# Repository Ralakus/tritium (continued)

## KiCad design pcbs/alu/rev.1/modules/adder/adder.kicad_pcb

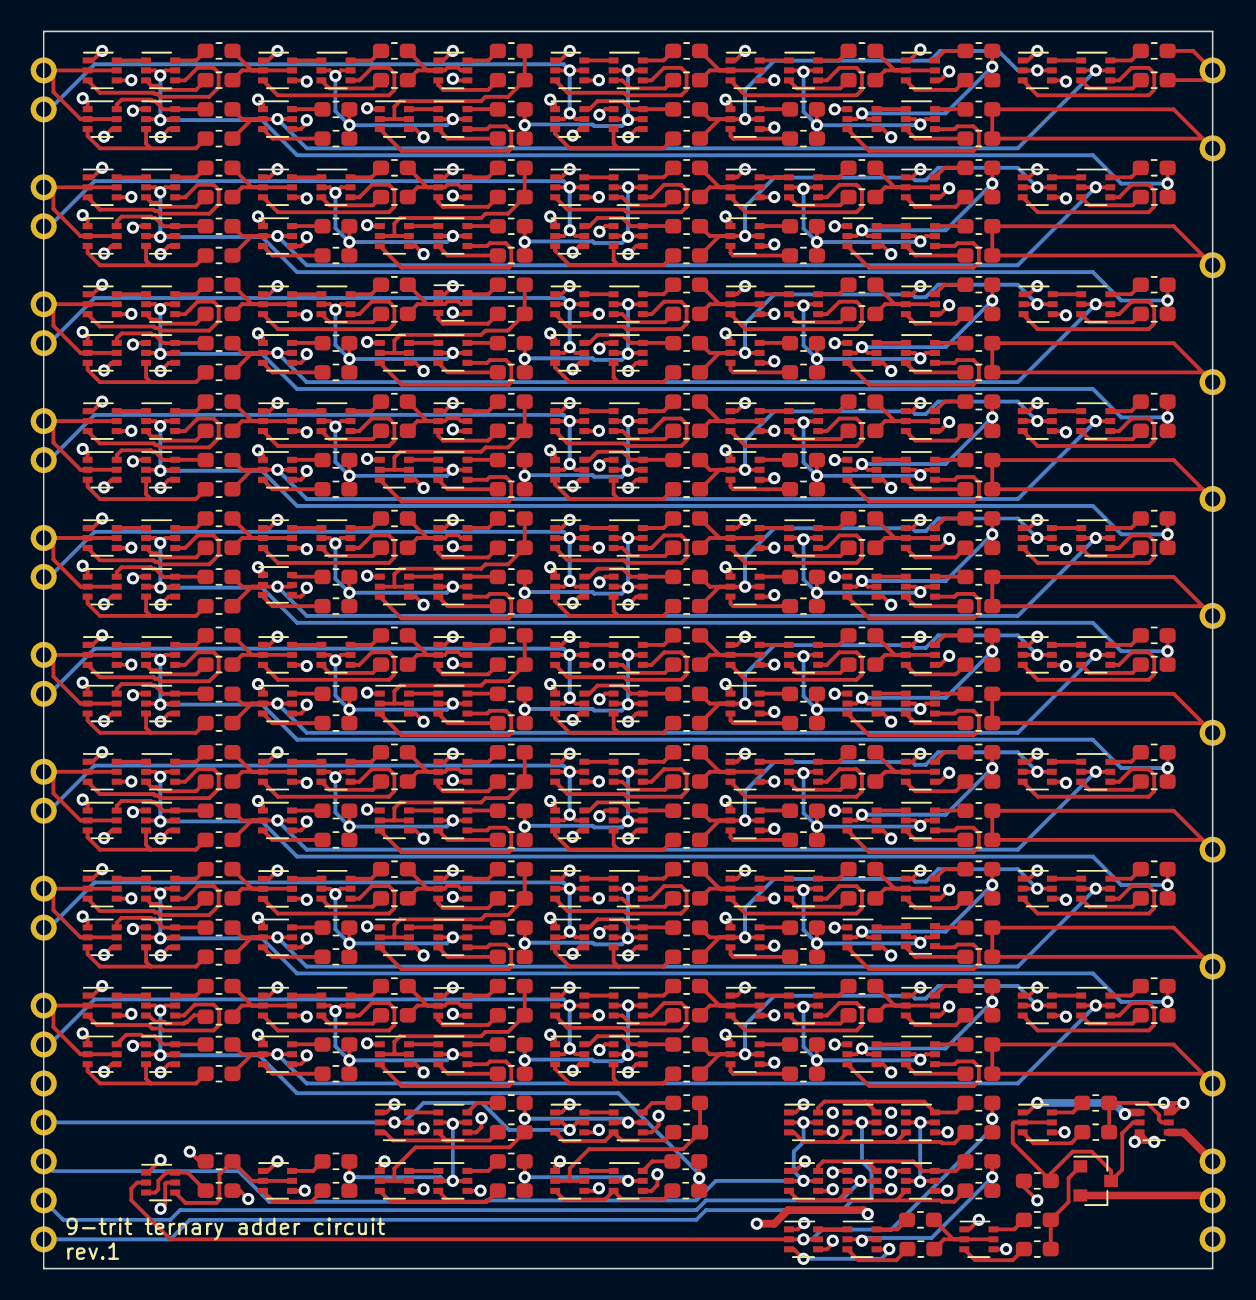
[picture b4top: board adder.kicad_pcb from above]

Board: 4 copper layers, 76.2 x 80.6 mm, 513 parts (0 on the bottom side), 544 nets.

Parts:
J1, J2, J3, J4, J5, J6, J7, J8, J9, J10, J11, J12, J13, J14, J15, J16, J17, J18, J19, J20, J21, J22, J23, J24, J25, J26, J27, J28, J29, J30, J31, J32, J33, J34, J35, J36: Conn_01x01; Edge_Castellation_1x01_P2.54
Q1, Q2, Q3, Q4, Q5, Q6, Q7, Q8, Q9, Q10, Q11, Q12, Q13, Q14, Q15, Q16, Q17, Q19, Q20, Q21, Q22, Q23, Q24, Q25, Q26, Q27, Q28, Q29, Q30, Q31, Q32, Q33, Q34, Q35, Q36, Q37, Q38, Q39, Q40, Q41, Q42, Q43, Q44, Q45, Q46, Q47, Q48, Q49, Q50, Q51, Q52, Q53, Q54, Q55, Q56, Q57, Q58, Q59, Q60, Q61, Q62, Q63, Q64, Q65, Q66, Q67, Q68, Q69, Q70, Q71, Q72, Q73, Q74, Q75, Q76, Q77, Q78, Q79, Q80, Q81, Q82, Q83, Q84, Q85, Q86, Q87, Q88, Q89, Q90, Q91, Q92, Q93, Q94, Q95, Q96, Q97, Q98, Q99, Q100, Q101, Q102, Q103, Q104, Q105, Q106, Q107, Q108, Q109, Q110, Q111, Q112, Q113, Q114, Q115, Q116, Q117, Q118, Q119, Q120, Q121, Q122, Q123, Q124, Q125, Q126, Q127, Q128, Q129, Q130, Q131, Q132, Q133, Q134, Q135, Q136, Q137, Q138, Q139, Q140, Q141, Q142, Q143, Q144, Q145, Q146, Q147, Q148, Q149, Q150, Q151, Q152, Q153, Q154, Q155, Q156, Q157, Q158, Q159, Q160, Q161, Q162, Q163, Q164, Q165, Q166, Q167, Q168, Q169, Q170, Q171, Q172, Q173, Q174, Q175, Q176, Q177, Q178, Q179, Q180, Q181, Q182, Q183, Q184, Q185, Q186, Q187, Q188, Q189, Q190, Q191, Q192, Q193, Q194, Q195, Q196, Q197, Q198, Q199, Q200, Q201, Q202, Q203, Q204, Q205, Q206, Q207, Q208, Q209, Q210, Q211, Q212, Q213, Q214, Q215, Q216, Q217, Q218, Q219, Q220: BSS8402DW; SOT-363_SC-70-6
Q18: 2N7002; SOT-23
R1, R3, R4, R5, R6, R7, R8, R9, R10, R11, R12, R13, R14, R15, R16, R17, R18, R19, R20, R21, R22, R23, R24, R25, R26, R27, R28, R29, R30, R31, R32, R33, R34, R35, R36, R37, R38, R39, R40, R41, R42, R43, R44, R45, R46, R47, R48, R49, R50, R51, R52, R53, R54, R55, R56, R57, R58, R59, R60, R61, R62, R63, R64, R65, R66, R67, R68, R69, R70, R71, R72, R73, R74, R75, R76, R77, R78, R79, R80, R81, R82, R83, R84, R85, R86, R87, R88, R89, R90, R91, R92, R93, R94, R95, R96, R97, R98, R99, R100, R101, R102, R103, R104, R105, R106, R107, R108, R109, R110, R111, R112, R113, R114, R115, R116, R117, R118, R119, R120, R121, R122, R123, R124, R125, R126, R127, R128, R129, R130, R131, R132, R133, R134, R135, R136, R137, R138, R139, R140, R141, R142, R143, R144, R145, R146, R147, R148, R149, R150, R151, R152, R153, R154, R155, R156, R157, R158, R159, R160, R161, R162, R163, R164, R165, R166, R167, R168, R169, R170, R171, R172, R173, R174, R175, R176, R177, R178, R179, R180, R181, R182, R183, R184, R185, R186, R187, R188, R189, R190, R191, R192, R193, R194, R195, R196, R197, R198, R199, R200, R201, R202, R203, R204, R205, R206, R207, R208, R209, R210, R211, R212, R213, R214, R215, R216, R217, R218, R219, R220, R221, R222, R223, R224, R225, R226, R227, R228, R229, R230, R231, R232, R233, R234, R235, R236, R237, R238, R239, R240, R241, R242, R243, R244, R245, R246, R247, R248, R249, R250, R251, R252, R253, R254, R255, R256, R257: 12k; R_0603_1608Metric_Pad1.05x0.95mm_HandSolder
R2: 470k; R_0603_1608Metric_Pad1.05x0.95mm_HandSolder

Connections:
/adder/CarryIn: Q29.2, Q29.5, Q32.2, Q32.5, R20.1, R21.2
/adder/Vdd: Q22.3, Q23.4, Q24.4, Q25.4, Q26.4, Q27.4, Q28.4, Q29.4, Q30.4, Q31.4, Q35.4, Q36.4, Q37.4, Q38.4, Q39.4, Q40.4, Q44.4, Q45.4, Q46.4, Q47.4, Q48.4, Q49.4, Q53.4, Q54.4, Q55.4, Q56.4, Q57.4, Q58.4, Q59.4, Q60.4, Q61.4, Q65.4, Q66.4, Q67.4, Q68.4, Q69.4, Q70.4, Q74.4, Q75.4, Q76.4, Q77.4, Q78.4, Q79.4, Q83.4, Q84.4, Q85.4, Q89.4, Q90.4, Q91.4, Q92.4, Q93.4, Q94.4, Q95.4, Q96.4, Q97.4, Q101.4, Q102.4, Q103.4, Q104.4, Q105.4, Q106.4, Q110.4, Q111.4, Q112.4, Q113.4, Q114.4, Q115.4, Q119.4, Q120.4, Q121.4, Q122.4, Q123.4, Q124.4, Q125.4, Q126.4, Q127.4, Q131.4, Q132.4, Q133.4, Q134.4, Q135.4, Q136.4, Q140.4, Q141.4, Q142.4, Q143.4, Q144.4, Q145.4, Q149.4, Q150.4, Q151.4, Q155.4, Q156.4, Q157.4, Q158.4, Q159.4, Q160.4, Q161.4, Q162.4, Q163.4, Q167.4, Q168.4, Q169.4, Q170.4, Q171.4, Q172.4, Q176.4, Q177.4, Q178.4, Q179.4, Q180.4, Q181.4, Q185.4, Q186.4, Q187.4, Q188.4, Q189.4, Q190.4, Q191.4, Q192.4, Q193.4, Q197.4, Q198.4, Q199.4, Q200.4, Q201.4, Q202.4, Q206.4, Q207.4, Q208.4, Q209.4, Q210.4, Q211.4, Q215.4, Q216.4, Q217.4
/adder/Vss: Q22.6, Q23.1, Q24.1, Q25.1, Q26.1, Q27.1, Q28.1, Q29.1, Q30.1, Q31.1, Q35.1, Q36.1, Q37.1, Q38.1, Q39.1, Q40.1, Q44.1, Q45.1, Q46.1, Q47.1, Q48.1, Q49.1, Q53.1, Q54.1, Q55.1, Q56.1, Q57.1, Q58.1, Q59.1, Q60.1, Q61.1, Q65.1, Q66.1, Q67.1, Q68.1, Q69.1, Q70.1, Q74.1, Q75.1, Q76.1, Q77.1, Q78.1, Q79.1, Q83.1, Q84.1, Q85.1, Q89.1, Q90.1, Q91.1, Q92.1, Q93.1, Q94.1, Q95.1, Q96.1, Q97.1, Q101.1, Q102.1, Q103.1, Q104.1, Q105.1, Q106.1, Q110.1, Q111.1, Q112.1, Q113.1, Q114.1, Q115.1, Q119.1, Q120.1, Q121.1, Q122.1, Q123.1, Q124.1, Q125.1, Q126.1, Q127.1, Q131.1, Q132.1, Q133.1, Q134.1, Q135.1, Q136.1, Q140.1, Q141.1, Q142.1, Q143.1, Q144.1, Q145.1, Q149.1, Q150.1, Q151.1, Q155.1, Q156.1, Q157.1, Q158.1, Q159.1, Q160.1, Q161.1, Q162.1, Q163.1, Q167.1, Q168.1, Q169.1, Q170.1, Q171.1, Q172.1, Q176.1, Q177.1, Q178.1, Q179.1, Q180.1, Q181.1, Q185.1, Q186.1, Q187.1, Q188.1, Q189.1, Q190.1, Q191.1, Q192.1, Q193.1, Q197.1, Q198.1, Q199.1, Q200.1, Q201.1, Q202.1, Q206.1, Q207.1, Q208.1, Q209.1, Q210.1, Q211.1, Q215.1, Q216.1, Q217.1
A0: J1.1, Q23.2, Q23.5, Q24.2, Q24.5
A1: J2.1, Q89.2, Q89.5, Q90.2, Q90.5
A2: J3.1, Q155.2, Q155.5, Q156.2, Q156.5
A3: J4.1, Q25.2, Q25.5, Q26.2, Q26.5
A4: J5.1, Q91.2, Q91.5, Q92.2, Q92.5
A5: J6.1, Q157.2, Q157.5, Q158.2, Q158.5
A6: J7.1, Q27.2, Q27.5, Q28.2, Q28.5
A7: J8.1, Q93.2, Q93.5, Q94.2, Q94.5
A8: J9.1, Q159.2, Q159.5, Q160.2, Q160.5
B0: J10.1, Q53.2, Q53.5, Q54.2, Q54.5
B1: J11.1, Q119.2, Q119.5, Q120.2, Q120.5
B2: J12.1, Q185.2, Q185.5, Q186.2, Q186.5
B3: J13.1, Q55.2, Q55.5, Q56.2, Q56.5
B4: J14.1, Q121.2, Q121.5, Q122.2, Q122.5
B5: J15.1, Q187.2, Q187.5, Q188.2, Q188.5
B6: J16.1, Q57.2, Q57.5, Q58.2, Q58.5
B7: J17.1, Q123.2, Q123.5, Q124.2, Q124.5
B8: J18.1, Q189.2, Q189.5, Q190.2, Q190.5
CarryIn: J20.1, Q9.2, Q9.5, Q13.2, Q13.5
CarryOut: J19.1, R256.1, R257.2
FnA0: J21.1, Q2.2, Q2.5, Q3.2, Q3.5
FnB0: J22.1, Q6.2, Q6.5
FnB1: J23.1, Q5.2, Q5.5
GND: J35.1, Q1.5, Q18.2, R2.1
unnamed: Q1.2, Q11.2, Q11.5, R5.1, R6.2
unnamed: Q1.3, Q1.6, R1.1
unnamed: Q1.4, Q4.2, Q4.5, R2.2
unnamed: Q2.3, Q5.3, Q7.3, R5.2
unnamed: Q2.6, Q5.6, Q7.6, R6.1
unnamed: Q3.3, Q6.3, Q8.3, R7.2
unnamed: Q3.6, Q6.6, Q8.6, R8.1
unnamed: Q4.3, R3.2
unnamed: Q4.6, R4.1
unnamed: Q9.6, Q10.1
unnamed: Q10.2, Q10.5, Q17.2, Q17.5, R3.1, R4.2
unnamed: Q9.3, Q10.3, R9.2
unnamed: Q10.6, R10.1
unnamed: Q11.3, Q12.4
unnamed: Q11.6, Q12.1
unnamed: Q12.2, Q12.5, R7.1, R8.2
unnamed: Q12.3, R11.2
unnamed: Q12.6, R12.1
unnamed: Q13.3, Q16.3, R15.2
unnamed: Q13.6, Q16.1
unnamed: Q14.2, Q14.5, Q16.2, Q16.5, R9.1, R10.2
unnamed: Q14.3, Q17.3, R17.2
unnamed: Q14.6, Q17.1
unnamed: Q15.2, Q15.5, R11.1, R12.2
unnamed: Q15.3, R13.2
unnamed: Q15.6, R14.1
unnamed: Q16.6, R16.1
unnamed: Q17.6, R18.1
unnamed: Q18.1, R13.1, R14.2
unnamed: Q18.3, Q21.2, Q21.5, Q22.2, R19.1
unnamed: Q19.2, Q19.5, R15.1, R16.2
unnamed: Q19.3, Q20.3, R20.2
unnamed: Q19.6, Q20.1
unnamed: Q20.2, Q20.5, R17.1, R18.2
unnamed: Q20.6, R21.1
unnamed: Q21.3, R22.2
unnamed: Q21.6, R23.1
unnamed: Q22.5, R22.1, R23.2
unnamed: Q23.3, Q32.4
unnamed: Q23.6, Q32.1
unnamed: Q24.3, Q29.3, R24.2
unnamed: Q24.6, Q29.6, R25.1
unnamed: Q25.3, Q33.4
unnamed: Q25.6, Q33.1
unnamed: Q26.3, Q30.3, R26.2
unnamed: Q26.6, Q30.6, R27.1
unnamed: Q27.3, Q34.4
unnamed: Q27.6, Q34.1
unnamed: Q28.3, Q31.3, R28.2
unnamed: Q28.6, Q31.6, R29.1
unnamed: Q30.2, Q30.5, Q33.2, Q33.5, R252.1, R253.2
unnamed: Q31.2, Q31.5, Q34.2, Q34.5, R254.1, R255.2
unnamed: Q32.3, R30.2
unnamed: Q32.6, R31.1
unnamed: Q33.3, R32.2
unnamed: Q33.6, R33.1
unnamed: Q34.3, R34.2
unnamed: Q34.6, R35.1
unnamed: Q35.2, Q35.5, Q86.2, Q86.5, R24.1, R25.2
unnamed: Q35.3, R36.2
unnamed: Q35.6, R37.1
unnamed: Q36.2, Q36.5, Q87.2, Q87.5, R26.1, R27.2
unnamed: Q36.3, R38.2
unnamed: Q36.6, R39.1
unnamed: Q37.2, Q37.5, Q88.2, Q88.5, R28.1, R29.2
unnamed: Q37.3, R40.2
unnamed: Q37.6, R41.1
unnamed: Q38.2, Q38.5, R30.1, R31.2
unnamed: Q38.3, Q41.4
unnamed: Q38.6, Q41.1
unnamed: Q39.2, Q39.5, R32.1, R33.2
unnamed: Q39.3, Q42.4
unnamed: Q39.6, Q42.1
unnamed: Q40.2, Q40.5, R34.1, R35.2
unnamed: Q40.3, Q43.4
unnamed: Q40.6, Q43.1
unnamed: Q41.2, Q41.5, Q50.2, Q50.5, R36.1, R37.2
unnamed: Q41.3, R42.2
unnamed: Q41.6, R43.1
unnamed: Q42.2, Q42.5, Q51.2, Q51.5, R38.1, R39.2
unnamed: Q42.3, R44.2
unnamed: Q42.6, R45.1
unnamed: Q43.2, Q43.5, Q52.2, Q52.5, R40.1, R41.2
unnamed: Q43.3, R46.2
unnamed: Q43.6, R47.1
unnamed: Q44.2, Q44.5, R42.1, R43.2
unnamed: Q44.3, R48.2
unnamed: Q44.6, R49.1
unnamed: Q45.2, Q45.5, R44.1, R45.2
unnamed: Q45.3, R50.2
unnamed: Q45.6, R51.1
unnamed: Q46.2, Q46.5, R46.1, R47.2
unnamed: Q46.3, R52.2
unnamed: Q46.6, R53.1
unnamed: Q47.2, Q47.5, R48.1, R49.2
unnamed: Q47.3, Q50.4
unnamed: Q47.6, Q50.1
unnamed: Q48.2, Q48.5, R50.1, R51.2
unnamed: Q48.3, Q51.4
unnamed: Q48.6, Q51.1
unnamed: Q49.2, Q49.5, R52.1, R53.2
unnamed: Q49.3, Q52.4
unnamed: Q49.6, Q52.1
unnamed: Q50.3, R54.2
unnamed: Q50.6, R55.1
unnamed: Q51.3, R56.2
unnamed: Q51.6, R57.1
unnamed: Q52.3, R58.2
unnamed: Q52.6, R59.1
unnamed: Q53.3, Q62.4
unnamed: Q53.6, Q62.1
unnamed: Q54.3, Q59.3, R60.2
unnamed: Q54.6, Q59.6, R61.1
unnamed: Q55.3, Q63.4
unnamed: Q55.6, Q63.1
unnamed: Q56.3, Q60.3, R62.2
unnamed: Q56.6, Q60.6, R63.1
unnamed: Q57.3, Q64.4
unnamed: Q57.6, Q64.1
unnamed: Q58.3, Q61.3, R64.2
unnamed: Q58.6, Q61.6, R65.1
unnamed: Q59.2, Q59.5, Q62.2, Q62.5, R54.1, R55.2
unnamed: Q60.2, Q60.5, Q63.2, Q63.5, R56.1, R57.2
unnamed: Q61.2, Q61.5, Q64.2, Q64.5, R58.1, R59.2
unnamed: Q62.3, R66.2
unnamed: Q62.6, R67.1
unnamed: Q63.3, R68.2
unnamed: Q63.6, R69.1
unnamed: Q64.3, R70.2
unnamed: Q64.6, R71.1
unnamed: Q65.2, Q65.5, Q83.2, Q83.5, R60.1, R61.2
unnamed: Q65.3, R72.2
unnamed: Q65.6, R73.1
unnamed: Q66.2, Q66.5, Q84.2, Q84.5, R62.1, R63.2
unnamed: Q66.3, R74.2
unnamed: Q66.6, R75.1
unnamed: Q67.2, Q67.5, Q85.2, Q85.5, R64.1, R65.2
unnamed: Q67.3, R76.2
unnamed: Q67.6, R77.1
unnamed: Q68.2, Q68.5, R66.1, R67.2
unnamed: Q68.3, Q71.4
unnamed: Q68.6, Q71.1
unnamed: Q69.2, Q69.5, R68.1, R69.2
unnamed: Q69.3, Q72.4
unnamed: Q69.6, Q72.1
unnamed: Q70.2, Q70.5, R70.1, R71.2
unnamed: Q70.3, Q73.4
unnamed: Q70.6, Q73.1
unnamed: Q71.2, Q71.5, Q80.2, Q80.5, R72.1, R73.2
unnamed: Q71.3, R78.2
unnamed: Q71.6, R79.1
unnamed: Q72.2, Q72.5, Q81.2, Q81.5, R74.1, R75.2
unnamed: Q72.3, R80.2
unnamed: Q72.6, R81.1
unnamed: Q73.2, Q73.5, Q82.2, Q82.5, R76.1, R77.2
unnamed: Q73.3, R82.2
unnamed: Q73.6, R83.1
unnamed: Q74.2, Q74.5, R78.1, R79.2
unnamed: Q74.3, R84.2
unnamed: Q74.6, R85.1
unnamed: Q75.2, Q75.5, R80.1, R81.2
unnamed: Q75.3, R86.2
unnamed: Q75.6, R87.1
unnamed: Q76.2, Q76.5, R82.1, R83.2
unnamed: Q76.3, R88.2
unnamed: Q76.6, R89.1
unnamed: Q77.2, Q77.5, R84.1, R85.2
unnamed: Q77.3, Q80.4
unnamed: Q77.6, Q80.1
unnamed: Q78.2, Q78.5, R86.1, R87.2
unnamed: Q78.3, Q81.4
unnamed: Q78.6, Q81.1
unnamed: Q79.2, Q79.5, R88.1, R89.2
unnamed: Q79.3, Q82.4
unnamed: Q79.6, Q82.1
unnamed: Q80.3, R90.2
unnamed: Q80.6, R91.1
unnamed: Q81.3, R92.2
unnamed: Q81.6, R93.1
unnamed: Q82.3, R94.2
unnamed: Q82.6, R95.1
unnamed: Q83.3, Q86.4
unnamed: Q83.6, Q86.1
unnamed: Q84.3, Q87.4
unnamed: Q84.6, Q87.1
unnamed: Q85.3, Q88.4
unnamed: Q85.6, Q88.1
unnamed: Q86.3, R96.2
unnamed: Q86.6, R97.1
unnamed: Q87.3, R98.2
unnamed: Q87.6, R99.1
unnamed: Q88.3, R100.2
unnamed: Q88.6, R101.1
unnamed: Q89.3, Q98.4
unnamed: Q89.6, Q98.1
unnamed: Q90.3, Q95.3, R102.2
unnamed: Q90.6, Q95.6, R103.1
unnamed: Q91.3, Q99.4
unnamed: Q91.6, Q99.1
unnamed: Q92.3, Q96.3, R104.2
unnamed: Q92.6, Q96.6, R105.1
unnamed: Q94.3, Q97.3, R106.2
unnamed: Q94.6, Q97.6, R107.1
unnamed: Q95.2, Q95.5, Q98.2, Q98.5, R96.1, R97.2
unnamed: Q96.2, Q96.5, Q99.2, Q99.5, R98.1, R99.2
unnamed: Q98.3, R108.2
unnamed: Q98.6, R109.1
unnamed: Q99.3, R110.2
unnamed: Q99.6, R111.1
unnamed: Q93.6, Q100.1
unnamed: Q97.2, Q97.5, Q100.2, Q100.5, R100.1, R101.2
unnamed: Q100.3, R112.2
unnamed: Q93.3, Q100.4
unnamed: Q100.6, R113.1
unnamed: Q101.2, Q101.5, Q152.2, Q152.5, R102.1, R103.2
unnamed: Q101.3, R114.2
unnamed: Q101.6, R115.1
unnamed: Q102.2, Q102.5, Q153.2, Q153.5, R104.1, R105.2
unnamed: Q102.3, R116.2
unnamed: Q102.6, R117.1
unnamed: Q103.2, Q103.5, Q154.2, Q154.5, R106.1, R107.2
unnamed: Q103.3, R118.2
unnamed: Q103.6, R119.1
unnamed: Q104.2, Q104.5, R108.1, R109.2
unnamed: Q104.3, Q107.4
unnamed: Q104.6, Q107.1
unnamed: Q105.2, Q105.5, R110.1, R111.2
unnamed: Q105.3, Q108.4
unnamed: Q105.6, Q108.1
unnamed: Q106.2, Q106.5, R112.1, R113.2
unnamed: Q106.3, Q109.4
unnamed: Q106.6, Q109.1
unnamed: Q107.2, Q107.5, Q116.2, Q116.5, R114.1, R115.2
unnamed: Q107.3, R120.2
unnamed: Q107.6, R121.1
unnamed: Q108.2, Q108.5, Q117.2, Q117.5, R116.1, R117.2
unnamed: Q108.3, R122.2
unnamed: Q108.6, R123.1
unnamed: Q109.2, Q109.5, Q118.2, Q118.5, R118.1, R119.2
unnamed: Q109.3, R124.2
unnamed: Q109.6, R125.1
unnamed: Q110.2, Q110.5, R120.1, R121.2
unnamed: Q110.3, R126.2
unnamed: Q110.6, R127.1
unnamed: Q111.2, Q111.5, R122.1, R123.2
unnamed: Q111.3, R128.2
unnamed: Q111.6, R129.1
unnamed: Q112.2, Q112.5, R124.1, R125.2
unnamed: Q112.3, R130.2
unnamed: Q112.6, R131.1
unnamed: Q113.2, Q113.5, R126.1, R127.2
unnamed: Q113.3, Q116.4
unnamed: Q113.6, Q116.1
unnamed: Q114.2, Q114.5, R128.1, R129.2
unnamed: Q114.3, Q117.4
unnamed: Q114.6, Q117.1
unnamed: Q115.2, Q115.5, R130.1, R131.2
unnamed: Q115.3, Q118.4
unnamed: Q115.6, Q118.1
unnamed: Q116.3, R132.2
unnamed: Q116.6, R133.1
unnamed: Q117.3, R134.2
unnamed: Q117.6, R135.1
unnamed: Q118.3, R136.2
unnamed: Q118.6, R137.1
unnamed: Q119.3, Q128.4
unnamed: Q119.6, Q128.1
unnamed: Q120.3, Q125.3, R138.2
unnamed: Q120.6, Q125.6, R139.1
unnamed: Q121.3, Q129.4
unnamed: Q121.6, Q129.1
unnamed: Q122.3, Q126.3, R140.2
unnamed: Q122.6, Q126.6, R141.1
unnamed: Q123.3, Q130.4
unnamed: Q123.6, Q130.1
unnamed: Q124.3, Q127.3, R142.2
unnamed: Q124.6, Q127.6, R143.1
unnamed: Q125.2, Q125.5, Q128.2, Q128.5, R132.1, R133.2
unnamed: Q126.2, Q126.5, Q129.2, Q129.5, R134.1, R135.2
unnamed: Q127.2, Q127.5, Q130.2, Q130.5, R136.1, R137.2
unnamed: Q128.3, R144.2
unnamed: Q128.6, R145.1
unnamed: Q129.3, R146.2
unnamed: Q129.6, R147.1
unnamed: Q130.3, R148.2
unnamed: Q130.6, R149.1
unnamed: Q131.2, Q131.5, Q149.2, Q149.5, R138.1, R139.2
unnamed: Q131.3, R150.2
unnamed: Q131.6, R151.1
unnamed: Q132.2, Q132.5, Q150.2, Q150.5, R140.1, R141.2
unnamed: Q132.3, R152.2
unnamed: Q132.6, R153.1
unnamed: Q133.2, Q133.5, Q151.2, Q151.5, R142.1, R143.2
unnamed: Q133.3, R154.2
unnamed: Q133.6, R155.1
unnamed: Q134.2, Q134.5, R144.1, R145.2
unnamed: Q134.3, Q137.4
unnamed: Q134.6, Q137.1
unnamed: Q135.2, Q135.5, R146.1, R147.2
unnamed: Q135.3, Q138.4
unnamed: Q135.6, Q138.1
unnamed: Q136.2, Q136.5, R148.1, R149.2
unnamed: Q136.3, Q139.4
unnamed: Q136.6, Q139.1
unnamed: Q137.2, Q137.5, Q146.2, Q146.5, R150.1, R151.2
unnamed: Q137.3, R156.2
unnamed: Q137.6, R157.1
unnamed: Q138.2, Q138.5, Q147.2, Q147.5, R152.1, R153.2
unnamed: Q138.3, R158.2
unnamed: Q138.6, R159.1
unnamed: Q139.2, Q139.5, Q148.2, Q148.5, R154.1, R155.2
unnamed: Q139.3, R160.2
unnamed: Q139.6, R161.1
unnamed: Q140.2, Q140.5, R156.1, R157.2
unnamed: Q140.3, R162.2
unnamed: Q140.6, R163.1
unnamed: Q141.2, Q141.5, R158.1, R159.2
unnamed: Q141.3, R164.2
unnamed: Q141.6, R165.1
unnamed: Q142.2, Q142.5, R160.1, R161.2
unnamed: Q142.3, R166.2
unnamed: Q142.6, R167.1
unnamed: Q143.2, Q143.5, R162.1, R163.2
unnamed: Q143.3, Q146.4
unnamed: Q143.6, Q146.1
unnamed: Q144.2, Q144.5, R164.1, R165.2
unnamed: Q144.3, Q147.4
unnamed: Q144.6, Q147.1
unnamed: Q145.2, Q145.5, R166.1, R167.2
unnamed: Q145.3, Q148.4
unnamed: Q145.6, Q148.1
unnamed: Q146.3, R168.2
unnamed: Q146.6, R169.1
unnamed: Q147.3, R170.2
unnamed: Q147.6, R171.1
unnamed: Q148.3, R172.2
unnamed: Q148.6, R173.1
unnamed: Q149.3, Q152.4
unnamed: Q149.6, Q152.1
unnamed: Q150.3, Q153.4
unnamed: Q150.6, Q153.1
unnamed: Q151.3, Q154.4
unnamed: Q151.6, Q154.1
unnamed: Q152.3, R174.2
unnamed: Q152.6, R175.1
unnamed: Q153.3, R176.2
unnamed: Q153.6, R177.1
unnamed: Q154.3, R178.2
unnamed: Q154.6, R179.1
unnamed: Q155.3, Q164.4
unnamed: Q155.6, Q164.1
unnamed: Q156.3, Q161.3, R180.2
unnamed: Q156.6, Q161.6, R181.1
unnamed: Q157.3, Q165.4
unnamed: Q157.6, Q165.1
unnamed: Q158.3, Q162.3, R182.2
unnamed: Q158.6, Q162.6, R183.1
unnamed: Q159.3, Q166.4
unnamed: Q159.6, Q166.1
unnamed: Q160.3, Q163.3, R184.2
unnamed: Q160.6, Q163.6, R185.1
unnamed: Q161.2, Q161.5, Q164.2, Q164.5, R174.1, R175.2
unnamed: Q162.2, Q162.5, Q165.2, Q165.5, R176.1, R177.2
unnamed: Q163.2, Q163.5, Q166.2, Q166.5, R178.1, R179.2
unnamed: Q164.3, R186.2
unnamed: Q164.6, R187.1
unnamed: Q165.3, R188.2
unnamed: Q165.6, R189.1
unnamed: Q166.3, R190.2
unnamed: Q166.6, R191.1
unnamed: Q167.2, Q167.5, Q218.2, Q218.5, R180.1, R181.2
unnamed: Q167.3, R192.2
unnamed: Q167.6, R193.1
unnamed: Q168.2, Q168.5, Q219.2, Q219.5, R182.1, R183.2
unnamed: Q168.3, R194.2
unnamed: Q168.6, R195.1
unnamed: Q169.2, Q169.5, Q220.2, Q220.5, R184.1, R185.2
unnamed: Q169.3, R196.2
unnamed: Q169.6, R197.1
unnamed: Q170.2, Q170.5, R186.1, R187.2
unnamed: Q170.3, Q173.4
unnamed: Q170.6, Q173.1
unnamed: Q171.2, Q171.5, R188.1, R189.2
unnamed: Q171.3, Q174.4
unnamed: Q171.6, Q174.1
unnamed: Q172.2, Q172.5, R190.1, R191.2
unnamed: Q172.3, Q175.4
unnamed: Q172.6, Q175.1
unnamed: Q173.2, Q173.5, Q182.2, Q182.5, R192.1, R193.2
unnamed: Q173.3, R198.2
unnamed: Q173.6, R199.1
unnamed: Q174.2, Q174.5, Q183.2, Q183.5, R194.1, R195.2
unnamed: Q174.3, R200.2
unnamed: Q174.6, R201.1
unnamed: Q175.2, Q175.5, Q184.2, Q184.5, R196.1, R197.2
unnamed: Q175.3, R202.2
unnamed: Q175.6, R203.1
unnamed: Q176.2, Q176.5, R198.1, R199.2
unnamed: Q176.3, R204.2
unnamed: Q176.6, R205.1
unnamed: Q177.2, Q177.5, R200.1, R201.2
unnamed: Q177.3, R206.2
unnamed: Q177.6, R207.1
unnamed: Q178.2, Q178.5, R202.1, R203.2
unnamed: Q178.3, R208.2
unnamed: Q178.6, R209.1
unnamed: Q179.2, Q179.5, R204.1, R205.2
unnamed: Q179.3, Q182.4
unnamed: Q179.6, Q182.1
unnamed: Q180.2, Q180.5, R206.1, R207.2
unnamed: Q180.3, Q183.4
unnamed: Q180.6, Q183.1
unnamed: Q181.2, Q181.5, R208.1, R209.2
unnamed: Q181.3, Q184.4
unnamed: Q181.6, Q184.1
unnamed: Q182.3, R210.2
unnamed: Q182.6, R211.1
unnamed: Q183.3, R212.2
unnamed: Q183.6, R213.1
unnamed: Q184.3, R214.2
unnamed: Q184.6, R215.1
unnamed: Q185.3, Q194.4
unnamed: Q185.6, Q194.1
unnamed: Q186.3, Q191.3, R216.2
unnamed: Q186.6, Q191.6, R217.1
unnamed: Q187.3, Q195.4
unnamed: Q187.6, Q195.1
unnamed: Q188.3, Q192.3, R218.2
unnamed: Q188.6, Q192.6, R219.1
unnamed: Q189.3, Q196.4
unnamed: Q189.6, Q196.1
unnamed: Q190.3, Q193.3, R220.2
unnamed: Q190.6, Q193.6, R221.1
unnamed: Q191.2, Q191.5, Q194.2, Q194.5, R210.1, R211.2
unnamed: Q192.2, Q192.5, Q195.2, Q195.5, R212.1, R213.2
unnamed: Q193.2, Q193.5, Q196.2, Q196.5, R214.1, R215.2
unnamed: Q194.3, R222.2
unnamed: Q194.6, R223.1
unnamed: Q195.3, R224.2
unnamed: Q195.6, R225.1
unnamed: Q196.3, R226.2
unnamed: Q196.6, R227.1
unnamed: Q197.2, Q197.5, Q215.2, Q215.5, R216.1, R217.2
unnamed: Q197.3, R228.2
unnamed: Q197.6, R229.1
unnamed: Q198.2, Q198.5, Q216.2, Q216.5, R218.1, R219.2
unnamed: Q198.3, R230.2
unnamed: Q198.6, R231.1
unnamed: Q199.2, Q199.5, Q217.2, Q217.5, R220.1, R221.2
unnamed: Q199.3, R232.2
unnamed: Q199.6, R233.1
unnamed: Q200.2, Q200.5, R222.1, R223.2
unnamed: Q200.3, Q203.4
unnamed: Q200.6, Q203.1
unnamed: Q201.2, Q201.5, R224.1, R225.2
unnamed: Q201.3, Q204.4
unnamed: Q201.6, Q204.1
unnamed: Q202.2, Q202.5, R226.1, R227.2
unnamed: Q202.3, Q205.4
unnamed: Q202.6, Q205.1
unnamed: Q203.2, Q203.5, Q212.2, Q212.5, R228.1, R229.2
unnamed: Q203.3, R234.2
unnamed: Q203.6, R235.1
unnamed: Q204.2, Q204.5, Q213.2, Q213.5, R230.1, R231.2
unnamed: Q204.3, R236.2
unnamed: Q204.6, R237.1
unnamed: Q205.2, Q205.5, Q214.2, Q214.5, R232.1, R233.2
unnamed: Q205.3, R238.2
unnamed: Q205.6, R239.1
unnamed: Q206.2, Q206.5, R234.1, R235.2
unnamed: Q206.3, R240.2
unnamed: Q206.6, R241.1
unnamed: Q207.2, Q207.5, R236.1, R237.2
unnamed: Q207.3, R242.2
unnamed: Q207.6, R243.1
unnamed: Q208.2, Q208.5, R238.1, R239.2
unnamed: Q208.3, R244.2
unnamed: Q208.6, R245.1
unnamed: Q209.2, Q209.5, R240.1, R241.2
unnamed: Q209.3, Q212.4
unnamed: Q209.6, Q212.1
unnamed: Q210.2, Q210.5, R242.1, R243.2
unnamed: Q210.3, Q213.4
unnamed: Q210.6, Q213.1
unnamed: Q211.2, Q211.5, R244.1, R245.2
unnamed: Q211.3, Q214.4
unnamed: Q211.6, Q214.1
unnamed: Q212.3, R246.2
unnamed: Q212.6, R247.1
unnamed: Q213.3, R248.2
unnamed: Q213.6, R249.1
unnamed: Q214.3, R250.2
unnamed: Q214.6, R251.1
unnamed: Q215.3, Q218.4
unnamed: Q215.6, Q218.1
unnamed: Q216.3, Q219.4
unnamed: Q216.6, Q219.1
unnamed: Q217.3, Q220.4
unnamed: Q217.6, Q220.1
unnamed: Q218.3, R252.2
unnamed: Q218.6, R253.1
unnamed: Q219.3, R254.2
unnamed: Q219.6, R255.1
unnamed: Q220.3, R256.2
unnamed: Q220.6, R257.1
OutputEnable: J24.1, Q7.2, Q7.5, Q8.2, Q8.5
R0: J25.1, R90.1, R91.2
R1: J26.1, R168.1, R169.2
R2: J27.1, R246.1, R247.2
R3: J28.1, R92.1, R93.2
R4: J29.1, R170.1, R171.2
R5: J30.1, R248.1, R249.2
R6: J31.1, R94.1, R95.2
R7: J32.1, R172.1, R173.2
R8: J33.1, R250.1, R251.2
Vdd: J34.1, Q2.4, Q3.4, Q4.4, Q5.4, Q6.4, Q7.4, Q8.4, Q9.4, Q10.4, Q11.4, Q13.4, Q14.4, Q15.4, Q16.4, Q17.4, Q19.4, Q20.4, Q21.4, Q22.4, R1.2, R19.2
Vss: J36.1, Q1.1, Q2.1, Q3.1, Q4.1, Q5.1, Q6.1, Q7.1, Q8.1, Q9.1, Q11.1, Q13.1, Q14.1, Q15.1, Q19.1, Q21.1, Q22.1
